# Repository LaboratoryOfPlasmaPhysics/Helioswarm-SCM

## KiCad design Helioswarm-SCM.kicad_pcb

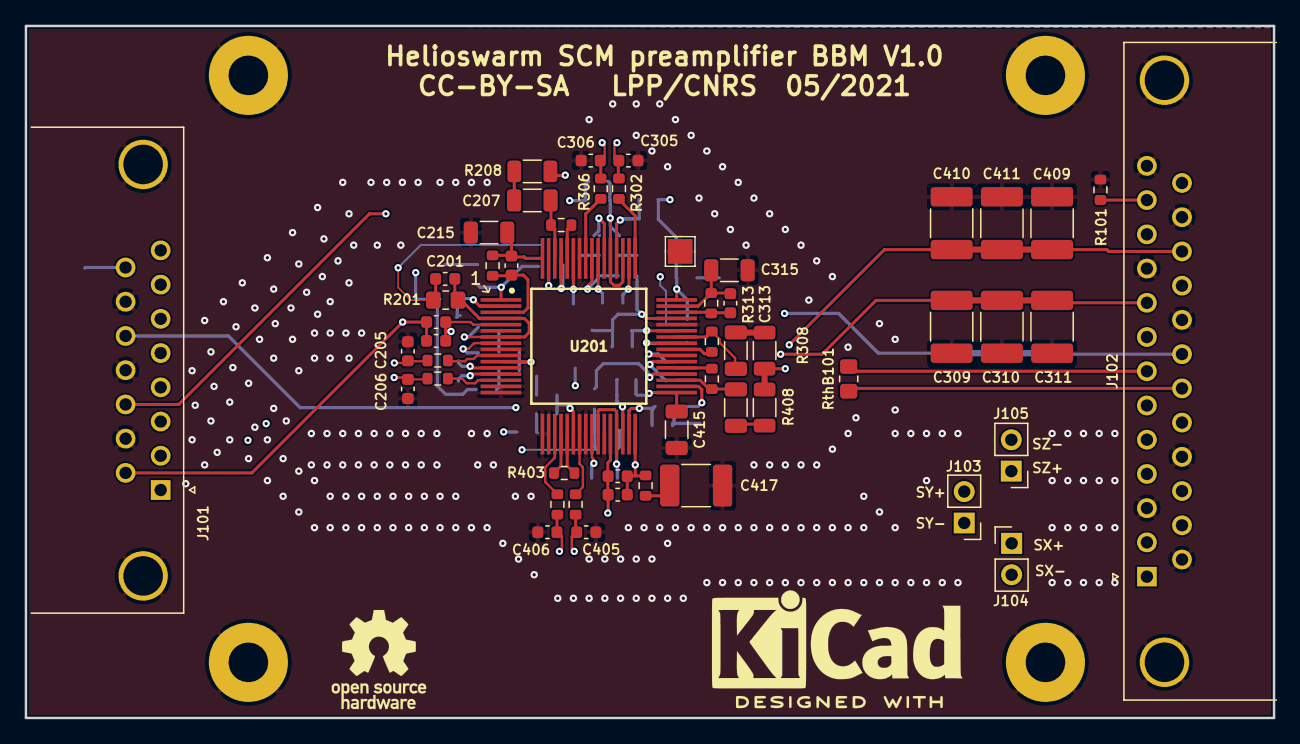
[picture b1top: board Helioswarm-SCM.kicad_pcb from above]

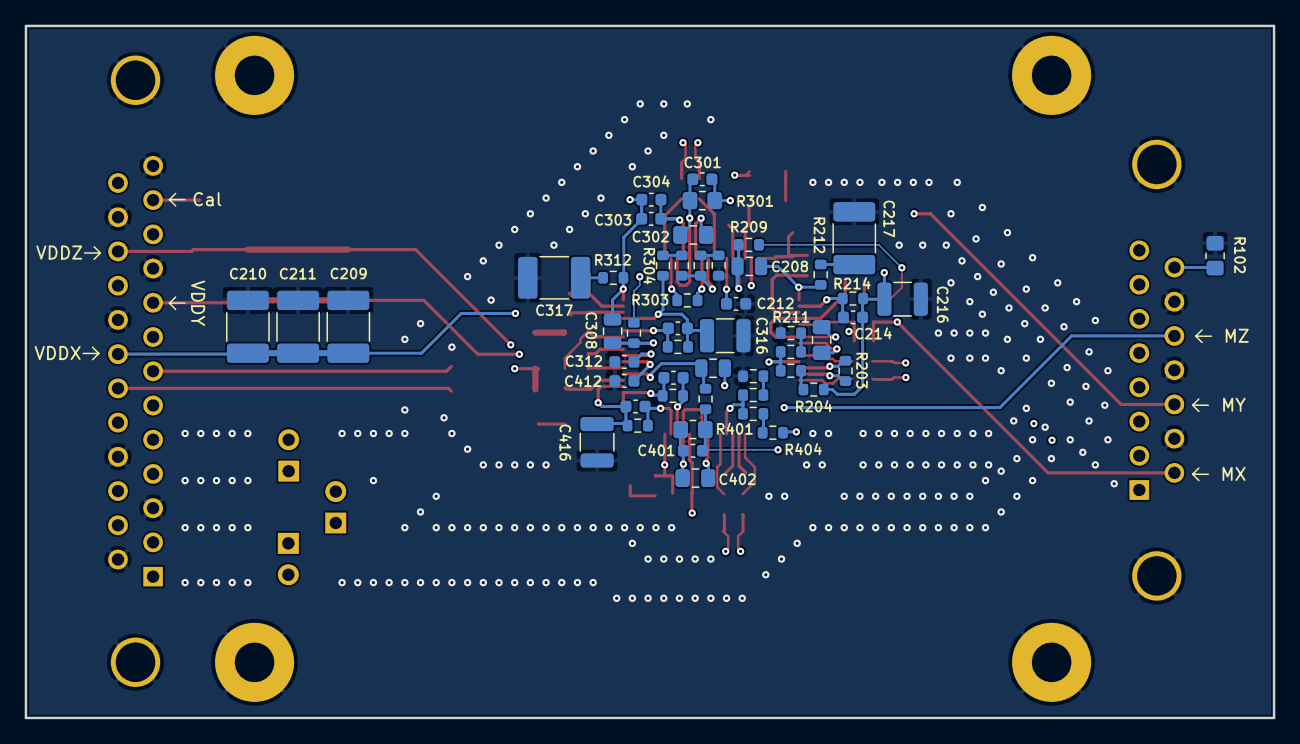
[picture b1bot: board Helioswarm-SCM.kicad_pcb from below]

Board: 4 copper layers, 101.0 x 56.0 mm, 109 parts (51 on the bottom side), 79 nets.

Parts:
C201, C203, C204, C205, C206, C301, C303, C304, C305, C306, C401, C403, C404, C405, C406: *; C_0603_1608Metric
C202, C302, C402: *; C_0805_2012Metric_Pad1.18x1.45mm_HandSolder
C207, C215, C307, C315, C407, C415: 220n; C_1206_3216Metric
C208, C308, C408: *; C_0805_2012Metric
C209, C210, C211, C309, C310, C311, C409, C410, C411: 680n; C_1812_4532Metric_Pad1.57x3.40mm_HandSolder
C212, C312, C412: 1n; C_0603_1608Metric
C213, C214, C313, C314, C413, C414: 221p; C_0603_1608Metric
C216, C316, C416: 470nF; C_1210_3225Metric
C217, C317, C417: 470n; C_1812_4532Metric_Pad1.57x3.40mm_HandSolder
H101, H102, H103, H104: MountingHole_Pad; MountingHole_3.2mm_M3_Pad
J101: DB15_Female_MountingHoles; DSUB-15_Female_Horizontal_P2.77x2.84mm_EdgePinOffset7.70mm_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
J102: DB25_Female_MountingHoles; DSUB-25_Male_Horizontal_P2.77x2.84mm_EdgePinOffset7.70mm_Ho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
J103, J104, J105: Conn_01x02; PinHeader_1x02_P2.54mm_Vertical
LOGO1: Logo_Open_Hardware_Small; KiCad-Logo2_8mm_SilkScreen
LOGO2: Logo_Open_Hardware_Small; OSHW-Logo_7.5x8mm_SilkScreen
N_CFP101: Housing_Pad; TestPoint_Pad_2.0x2.0mm
R101: 10k; R_0603_1608Metric
R102: c-c; R_0805_2012Metric_Pad1.20x1.40mm_HandSolder
R201, R301, R401: 150k; R_0805_2012Metric_Pad1.20x1.40mm_HandSolder
R202, R206, R302, R306, R402, R406: 49,9; R_0603_1608Metric
R203, R303, R403: 7,68k; R_0603_1608Metric
R204, R211, R304, R311, R404, R411: 49,9k; R_0603_1608Metric
R205, R207, R305, R307, R405, R407: TBD; R_0603_1608Metric
R208, R308, R408: 750k; R_1206_3216Metric
R209, R309, R409: 42,2k; R_0603_1608Metric
R210, R310, R410: 24,9k; R_0603_1608Metric
R212, R312, R412: 400; R_0603_1608Metric
R213, R313, R413: 22,1k; R_0603_1608Metric
R214, R314, R414: 44,2k; R_0603_1608Metric
RthB101: 1k; R_0805_2012Metric_Pad1.20x1.40mm_HandSolder
U201: ASIC_JUICE; ASIC_Juice_CQFP-64

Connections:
/ASIC_X_Channel/In1N: C202.1, U201.8
/ASIC_X_Channel/In2P: C201.2, C202.2, R201.1, U201.4, U201.7
/ASIC_X_Channel/VDD: C214.1, C216.1, R204.2, R214.1, U201.63
/ASIC_Y_Channel/In1N: C302.1, U201.54
/ASIC_Y_Channel/In2P: C301.2, C302.2, R301.1, U201.51, U201.53
/ASIC_Y_Channel/VDD: C314.1, C316.1, R304.2, R314.1, U201.45
/ASIC_Z_Channel/In1N: C402.1, U201.25
/ASIC_Z_Channel/In2P: C401.2, C402.2, R401.1, U201.26, U201.29
/ASIC_Z_Channel/VDD: C414.1, C416.1, R404.2, R414.1, U201.34
/CAL: J102.12, R101.1, R208.2, R308.2, R408.2
/CR_X: C201.1, J101.2, R201.2, R209.2
/CR_Y: C301.1, J101.4, R301.2, R309.2
/CR_Z: C401.1, J101.6, R401.2, R409.2
/Chassis: J101.15, R102.1
/M_X: C203.1, C204.1, C208.2, J101.9, R212.1, U201.1
/M_Y: C303.1, C304.1, C308.2, J101.11, R312.1, U201.48
/M_Z: C403.1, C404.1, C408.2, J101.13, R412.1, U201.32
/PCB_TEMP_SENSOR_1: J102.19, RthB101.1
/PCB_TEMP_SENSOR_2: J102.7, RthB101.2
/SCM_TEMP_SENSOR_1: J101.7, J102.18
/SCM_TEMP_SENSOR_2: J101.8, J102.6
/SCM_X: C203.2, C204.2, J101.1, U201.5
/SCM_Y: C303.2, C304.2, J101.3, U201.52
/SCM_Z: C403.2, C404.2, J101.5, U201.28
/SX+: C205.1, J102.2, J104.1, R202.1
/SX-: C206.2, J102.1, J104.2, R206.1
/SY+: C305.1, J102.15, J103.1, R302.1
/SY-: C306.2, J102.16, J103.2, R306.1
/SZ+: C405.1, J102.4, J105.1, R402.1
/SZ-: C406.2, J102.5, J105.2, R406.1
/VDD_X: C209.1, C210.1, C211.1, C212.1, J102.20, U201.59
/VDD_Y: C309.1, C310.1, C311.1, C312.1, J102.9, U201.39
/VDD_Z: C409.1, C410.1, C411.1, C412.1, J102.23, U201.38
GND: C205.2, C206.1, C209.2, C210.2, C211.2, C212.2, C215.2, C216.2, C217.2, C305.2, C306.1, C309.2, C310.2, C311.2, C312.2, C315.2, C316.2, C317.2, C405.2, C406.1, C409.2, C410.2, C411.2, C412.2, C415.2, C416.2, C417.2, H101.1, H102.1, H103.1, H104.1, J101.0, J101.10, J101.12, J101.14, J102.0, J102.3, J102.10, J102.13, J102.14, J102.17, J102.21, J102.24, N_CFP101.1, R101.2, R102.2, R211.2, R311.2, R411.2, U201.6, U201.9, U201.15, U201.16, U201.17, U201.18, U201.24, U201.27, U201.44, U201.58
unnamed: C207.1, R210.2, U201.62
unnamed: C207.2, R208.1
unnamed: C208.1, R209.1, U201.61
unnamed: C213.1, C215.1, R213.1, U201.64
unnamed: C213.2, R213.2, U201.3
unnamed: C214.2, R214.2, U201.2
unnamed: C217.1, R212.2
unnamed: C307.1, R310.2, U201.42
unnamed: C307.2, R308.1
unnamed: C308.1, R309.1, U201.41
unnamed: C313.1, C315.1, R313.1, U201.47
unnamed: C313.2, R313.2, U201.46
unnamed: C314.2, R314.2, U201.43
unnamed: C317.1, R312.2
unnamed: C407.1, R410.2, U201.35
unnamed: C407.2, R408.1
unnamed: C408.1, R409.1, U201.36
unnamed: C413.1, C415.1, R413.1, U201.33
unnamed: C413.2, R413.2, U201.30
unnamed: C414.2, R414.2, U201.31
unnamed: C417.1, R412.2
unnamed: R202.2, U201.10
unnamed: R203.1, U201.13
unnamed: R203.2, U201.12
unnamed: R204.1, R205.2
unnamed: R205.1, R207.1, U201.11
unnamed: R206.2, U201.14
unnamed: R207.2, R211.1
unnamed: R210.1, U201.60
unnamed: R302.2, U201.49
unnamed: R303.1, U201.50
unnamed: R303.2, U201.55
unnamed: R304.1, R305.2
unnamed: R305.1, R307.1, U201.56
unnamed: R306.2, U201.57
unnamed: R307.2, R311.1
unnamed: R310.1, U201.40
unnamed: R402.2, U201.23
unnamed: R403.1, U201.20
unnamed: R403.2, U201.21
unnamed: R404.1, R405.2
unnamed: R405.1, R407.1, U201.22
unnamed: R406.2, U201.19
unnamed: R407.2, R411.1
unnamed: R410.1, U201.37

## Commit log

2021-03-22 Repo init from JUICE design
2021-03-27 Set new template with LPP logo and CC-BY-SA license
2021-03-27 Simplified schematic and reset(cleared) PCB
2021-03-28 More sch cleaup
2021-04-26 Improved schematic net naming and started layout
2021-04-29 Fixed SCH mistakes and Layout WIP
2021-05-03 Layout WIP
    Asic mostly routed, D-Sub connectors layout started.
2021-05-04 PCB layout complete without silkscreen
2021-05-07 BBM PCB ready for review
2021-05-14 adds ASIC 3d model
2021-05-30 Updated BOM, and changed PCB origin.

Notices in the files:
Helioswarm-SCM.kicad_pcb:
CC-BY-SA LPP/CNRS  05/2021
